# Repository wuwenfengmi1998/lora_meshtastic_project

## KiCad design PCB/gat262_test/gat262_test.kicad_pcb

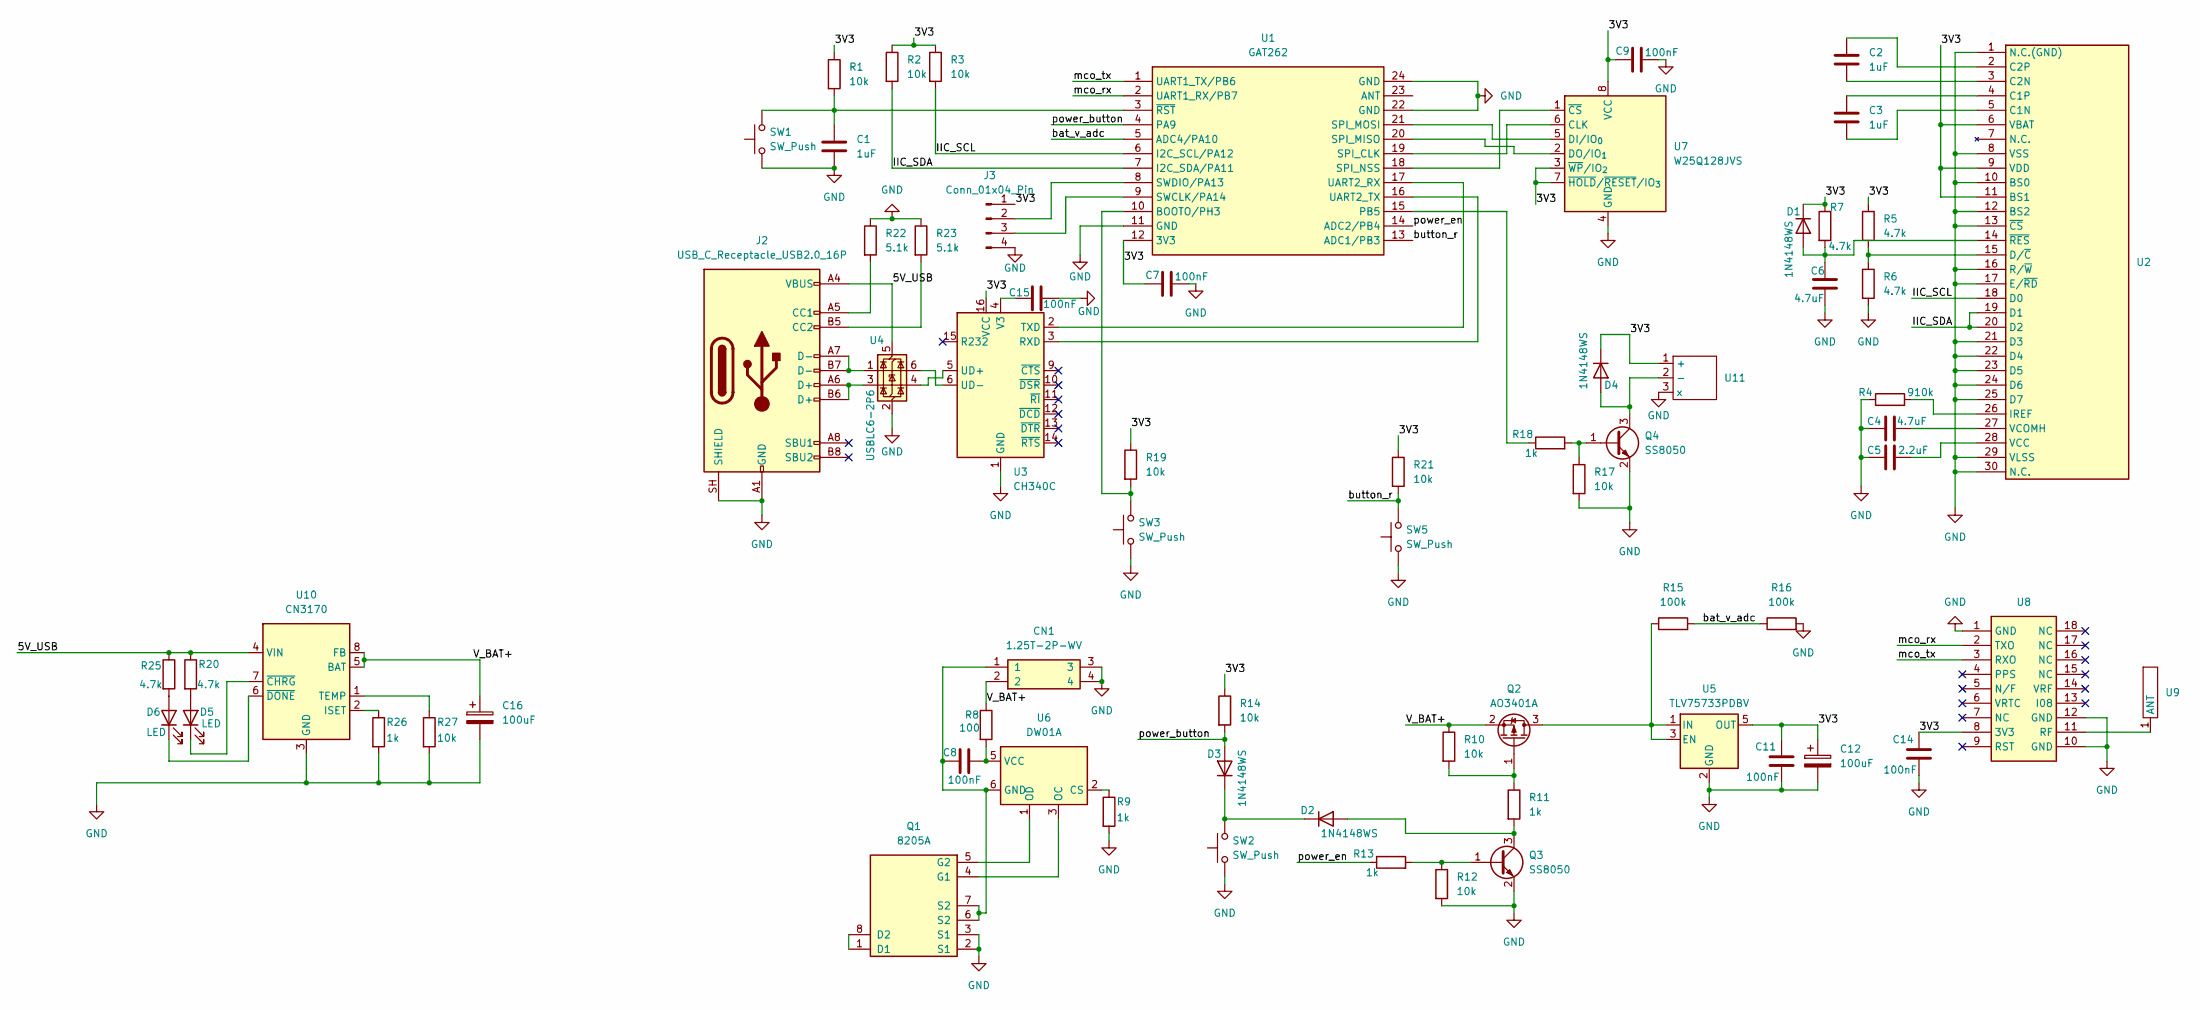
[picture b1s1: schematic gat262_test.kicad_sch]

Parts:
C1, C2, C3: 1uF; C_0805_2012Metric
C4, C6: 4.7uF; C_0805_2012Metric
C5: 2.2uF; C_0805_2012Metric
C7, C8, C9, C11, C14, C15: 100nF; C_0805_2012Metric
C12, C16: 100uF; CP_Elec_5x5.4
CN1: 1.25T-2P-WV; MPN 1.25T-2P-WV
D1, D2, D3, D4: 1N4148WS; D_SOD-323_HandSoldering
D5, D6: LED; LED_0603_1608Metric
J2: USB_C_Receptacle_USB2.0_16P; USB_C_Receptacle_G-Switch_GT-USB-7010ASV
J3: Conn_01x04_Pin; PinSocket_1x04_P2.54mm_Vertical
Q1: 8205A; MPN 8205A
Q2: AO3401A; SOT-23
Q3, Q4: SS8050; SOT-23-3
R1, R2, R3, R10, R12, R14, R17, R19, R21, R27: 10k; R_0603_1608Metric
R4: 910k; R_0603_1608Metric
R5, R6, R7, R20, R25: 4.7k; R_0603_1608Metric
R8: 100; R_0603_1608Metric
R9, R11, R13, R18, R26: 1k; R_0603_1608Metric
R15, R16: 100k; R_0603_1608Metric
R22, R23: 5.1k; R_0603_1608Metric
SW1, SW2, SW3, SW5: SW_Push; SW_SPST_B3U-1000P
U1: GAT262
U2: OLED_128_64
U3: CH340C; SOIC-16_3.9x9.9mm_P1.27mm
U4: USBLC6-2P6; SOT-23-6
U5: TLV75733PDBV; SOT-23-5
U6: DW01A; SOT-23-6
U7: W25Q128JVS; SOIC-8_5.3x5.3mm_P1.27mm
U8: gp02
U9: gps天线
U10: CN3170; SOIC-8-1EP_3.9x4.9mm_P1.27mm_EP2.41x3.3mm_ThermalVias
U11: 5050蜂鸣器

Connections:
/3V3: C7.1, C9.1, C11.2, C12.1, C14.2, D1.1 (K), D4.1 (K), J3.1, R1.1, R2.1, R3.1, R5.1, R7.1, R14.1, R19.1, R21.1, U1.12 (3V3), U2.6 (VBAT), U2.9 (VDD), U2.11 (BS1), U3.16 (VCC), U5.5 (OUT), U7.3 (~WP/IO_{2}), U7.7 (~HOLD/~RESET/IO_{3}), U7.8 (VCC), U8.8 (3V3), U11.1 (+)
/5V_USB: J2.A4 (VBUS), J2.A9 (VBUS), J2.B4 (VBUS), J2.B9 (VBUS), R20.1, R25.1, U4.5 (VBUS), U10.4 (VIN)
/IIC_SCL: R3.2, U1.6 (I2C_SCL/PA12), U2.18 (D0)
/IIC_SDA: R2.2, U1.7 (I2C_SDA/PA11), U2.19 (D1), U2.20 (D2)
/V_BAT+: C16.1, CN1.2, Q2.2 (S), R8.1, R10.1, U10.5 (BAT), U10.8 (FB)
/bat_v_adc: R15.2, R16.1, U1.5 (ADC4/PA10)
/button_r: R21.2, SW5.2, U1.13 (ADC1/PB3)
/mco_rx: U1.2 (UART1_RX/PB7), U8.2 (TXO)
/mco_tx: U1.1 (UART1_TX/PB6), U8.3 (RXO)
/power_button: D3.2 (A), R14.2, U1.4 (PA9)
/power_en: R13.1, U1.14 (ADC2/PB4)
GND: C1.2, C4.1, C5.1, C6.1, C7.2, C9.2, C11.1, C12.2, C14.1, C15.2, C16.2, CN1.3, CN1.4, J2.A1 (GND), J2.A12 (GND), J2.B1 (GND), J2.B12 (GND), J2.SH (SHIELD), J3.4, Q1.2 (S1), Q1.3 (S1), Q3.2 (E), Q4.2 (E), R4.1, R6.2, R9.2, R12.2, R16.2, R17.2, R22.1, R23.1, R26.2, R27.2, SW1.1, SW2.1, SW3.1, SW5.1, U1.11 (GND), U1.22 (GND), U1.24 (GND), U2.1 (N.C.(GND)), U2.8 (VSS), U2.10 (BS0), U2.12 (BS2), U2.13 (~CS), U2.16 (R/~W), U2.17 (E/~RD), U2.21 (D3), U2.22 (D4), U2.23 (D5), U2.24 (D6), U2.25 (D7), U2.29 (VLSS), U2.30 (N.C.), U3.1 (GND), U4.2 (GND), U5.2 (GND), U7.4 (GND), U8.1 (GND), U8.10 (GND), U8.12 (GND), U10.3 (GND), U10.9 (GND), U11.3 (x)
unnamed: C6.2, D1.2 (A), R7.2, U2.14 (~RES)
unnamed: D2.2 (A), Q3.3 (C), R11.2
unnamed: D2.1 (K), D3.1 (K), SW2.2
unnamed: D4.2 (A), Q4.3 (C), U11.2 (-)
unnamed: D5.2 (A), R20.2
unnamed: D5.1 (K), U10.7 (~CHRG)
unnamed: D6.2 (A), R25.2
unnamed: D6.1 (K), U10.6 (~DONE)
unnamed: J2.A5 (CC1), R22.2
unnamed: J2.B5 (CC2), R23.2
unnamed: J2.A6 (D+), J2.B6 (D+), U4.3 (I/O2)
unnamed: J2.A7 (D-), J2.B7 (D-), U4.1 (I/O1)
unnamed: J3.2, U1.8 (SWDIO/PA13)
unnamed: J3.3, U1.9 (SWCLK/PA14)
unnamed: Q1.1 (D1), Q1.8 (D2)
unnamed: Q1.4 (G1), U6.3 (OC)
unnamed: Q1.5 (G2), U6.1 (OD)
unnamed: Q2.3 (D), R15.1, U5.1 (IN), U5.3 (EN)
unnamed: Q2.1 (G), R10.2, R11.1
unnamed: Q3.1 (B), R12.1, R13.2
unnamed: Q4.1 (B), R17.1, R18.2
unnamed: R19.2, SW3.2, U1.10 (BOOTO/PH3)
unnamed: R18.1, U1.15 (PB5)
unnamed: U1.19 (SPI_CLK), U7.6 (CLK)
unnamed: U1.20 (SPI_MISO), U7.2 (DO/IO_{1})
unnamed: U1.21 (SPI_MOSI), U7.5 (DI/IO_{0})
unnamed: U1.18 (SPI_NSS), U7.1 (~CS)
unnamed: U1.17 (UART2_RX), U3.2 (TXD)
unnamed: U1.16 (UART2_TX), U3.3 (RXD)
unnamed: C1.1, R1.2, SW1.2, U1.3 (~RST)
unnamed: C3.2, U2.5 (C1N)
unnamed: C3.1, U2.4 (C1P)
unnamed: C2.2, U2.3 (C2N)
unnamed: C2.1, U2.2 (C2P)
unnamed: R5.2, R6.1, U2.15 (D/~C)
unnamed: R4.2, U2.26 (IREF)
unnamed: C5.2, U2.28 (VCC)
unnamed: C4.2, U2.27 (VCOMH)
unnamed: U3.5 (UD+), U4.4 (I/O2)
unnamed: U3.6 (UD-), U4.6 (I/O1)
unnamed: C15.1, U3.4 (V3)
unnamed: R9.1, U6.2 (CS)
unnamed: C8.1, CN1.1, Q1.6 (S2), Q1.7 (S2), U6.6 (GND)
unnamed: C8.2, R8.2, U6.5 (VCC)
unnamed: U8.11 (RF), U9.1 (ANT_1)
unnamed: R26.1, U10.2 (ISET)
unnamed: R27.1, U10.1 (TEMP)

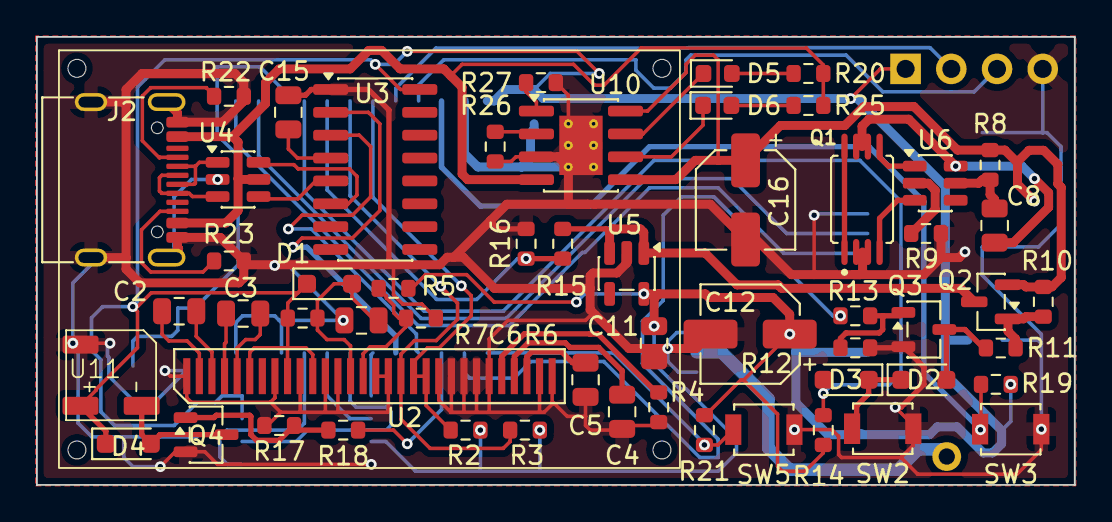
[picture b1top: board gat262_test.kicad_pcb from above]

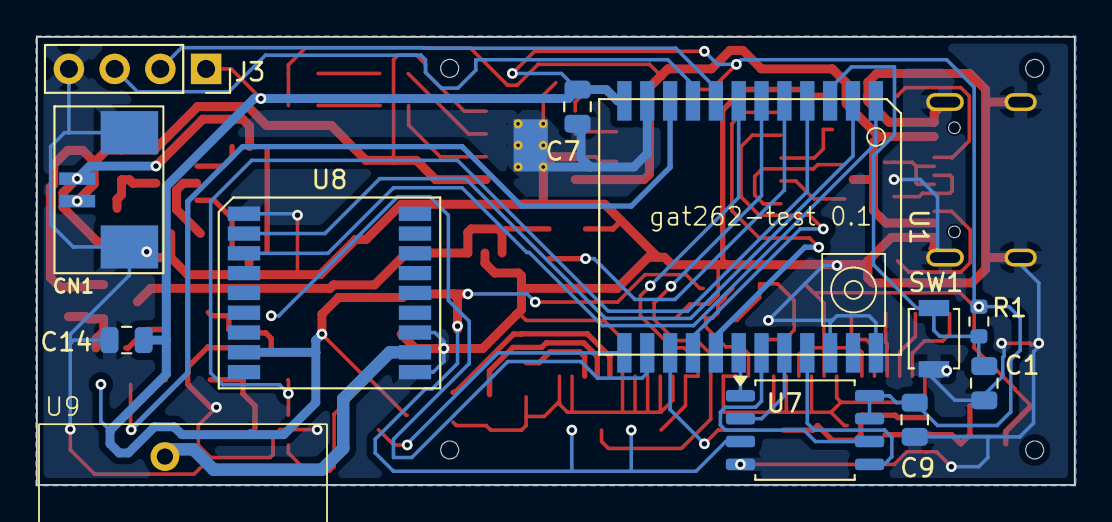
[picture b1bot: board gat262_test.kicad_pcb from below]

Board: 2 copper layers, 57.7 x 24.9 mm, 68 parts (12 on the bottom side), 59 nets.

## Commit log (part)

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2026-02-19 Add Demo Signed-off-by: kevin <kevin@lmve.net>
2026-02-20 已绘制原理图
2026-02-21 PCB 已完成 Signed-off-by: kevin <kevin@lmve.net>
2026-02-21 MV 版本原理图完成 Signed-off-by: kevin <kevin@lmve.net>
2026-02-22 MV版本PCBOK Signed-off-by: kevin <kevin@lmve.net>
2026-02-27 加入技术手册 Signed-off-by: 吴文峰 <kevin@lmve.net>
2026-03-02 PCB 更新到版本2 Signed-off-by: 吴文峰 <kevin@lmve.net>
2026-03-04 增加mv版本
2026-03-04 增加SETTING_MAX_POWER参数，
2026-03-04 增加屏幕支持
2026-03-04 加入GPS
2026-03-04 加入adc 加入led
2026-03-06 up Signed-off-by: 吴文峰 <kevin@lmve.net>
2026-03-06 稳定版代码 Signed-off-by: 吴文峰 <kevin@lmve.net>
2026-03-06 加密似乎ok了
2026-03-09 增加e22-400M33S Signed-off-by: kevin <kevin@lmve.net>
2026-03-09 3D Signed-off-by: kevin <kevin@lmve.net>
2026-03-19 新版本原理图 Signed-off-by: 吴文峰 <kevin@lmve.net>
2026-03-19 旅行版PCB画完 Signed-off-by: 吴文峰 <kevin@lmve.net>
2026-03-21 SETTING_MAX_POWER
2026-03-22 修复固件功率bug 实际功率需要用户自行计算 Signed-off-by: kevin <kevin@lmve.net>
2026-03-28 feat(travelers): TCA9535 矩阵键盘驱动 + 电源管理 + LoRa RST 虚拟引脚
    - 新增 TCA9535ButtonThread 驱动 (4x4 矩阵键盘, 中断/轮询模式)
    - 电源管理: P1.2 POWER_EN (MOS 供电) + P1.3 POWER_BOOT (2s 开/关机)
    - LoRa RST 通过 TCA9535 P1.4 + TCA9535GpioHal 虚拟引脚 200 控制
    - 修复 LTO 链接错误 (去掉 .h/.cpp 中的 HAS_TCA9535_BUTTON 守卫)
    - 新增 CHANGELOG.md, 更新 readme.md (PCAL9535 升级计划)
2026-03-28 feat(travelers): 矩阵按键映射改为 key3/7/11/15 方向键, P1.5 独立闪烁, 修复 cols 整数提升 bug
2026-03-28 feat(travelers): enable GPS with GP-02 module support
    - Add HAS_GPS=1, GPS_RX_PIN=20, GPS_TX_PIN=21
    - Add TCA9535 P1.6 (GPS RST) and P1.7 (GPS EN) control via I2C
    - GPS power on at boot: P1.6 and P1.7 default HIGH in init
    - Bridge gps->enablePin to TCA9535 via GpioUnaryTransformer
    - Add tca9535GpsReset() and tca9535GpsEn() static functions
    - Update CHANGELOG with GPS support details
2026-03-29 feat(travelers): TCA9535 充电检测 + 键盘背光 + isVbusIn 修复
    - 新增 P1.1 CHARGE_DET 充电检测（高电平=充电中），轮询间隔 2s
    - Power.cpp isCharging()/isVbusIn() 均使用 TCA9535_CHARGE_DET_PIN 分支
    - 新增 P1.0 键盘背光（高电平点亮），按键时亮，5s 无操作自动熄灭
    - 修复开机供电维持：POWER_EN 在 Wire.begin() 后立即锁定
    - 修复 P1 config 寄存器值 0x0A（之前 0x8D 导致 P1.2 高阻断电）
    - ⚠️ 已知问题：TP4057 电压反串导致未充电时 P1.1 仍读高，需硬件修改
2026-03-29 feat: 开机确认窗口 + 快捷回复/九宫格导航 + 充电检测加速
2026-03-29 feat(T9): 九宫格输入法 + 多项 bug 修复
    - T9 multi-tap 输入法：abc/ABC/123 三模式切换
    - 修复 commitMultiTap 无限递归崩溃（重入保护）
    - 修复 payload 残留导致非预期行为
    - 修复 REGENERATE_FRAMESET 重复触发导致跳回主页面
    - 修复大小写模式下出现数字（t9LetterMap 重做）
    - 修复光标不跟随预览字符跳转（displayCursor +1）
2026-03-29 feat: add Chinese 12x12 bitmap font (21075 glyphs) and fix boot gate
    - Add ChineseFont12x12.h: U+4E00-U+9FFF CJK coverage, 535KB flash
    - Add gen_chinese_font.mjs: @napi-rs/canvas based font generator tool
    - Enable CJK rendering in MessageRenderer and CannedMessageModule
    - Remove boot confirmation gate (required 2s button hold, caused shutdown loop)
    - Update partition table: app 2.75MB, OTA 192KB, spiffs 1MB
    - Update CHANGELOG
2026-03-29 up，中文字符显示向下挪动两个像素
2026-03-30 fix: 修复 NodeInfo 不广播节点名字和公钥问题
    - AdminModule: 显式同步 owner.role = config.device.role
    - NodeDB: CLIENT/CLIENT_MUTE 切回后恢复广播间隔
    修复从 CLIENT_HIDDEN 切换回 CLIENT 后 NodeInfo 永不广播的问题
2026-03-30 feat: 主页按*进入自由文本输入模式
    - 移除 INACTIVE 状态下 UP/DOWN 按键触发快捷回复列表的逻辑
    - 按 * 键直接进入 FREETEXT 模式
2026-03-30 fix: 修复 INACTIVE 状态下 UP/DOWN 仍能进入快捷回复的问题
    - handleMessageSelectorInput() 在 INACTIVE 状态时直接返回 false
    - 按 * 键进入 FREETEXT 模式
2026-03-30 fix: 启用 CANNED_MESSAGE_MODULE_ENABLE
    - 在 variant.h 中添加 CANNED_MESSAGE_MODULE_ENABLE=1
    - 确保 CannedMessageModule 正确注册到 inputBroker
2026-03-30 debug: 添加 INACTIVE 状态输入事件日志
2026-03-30 debug: 添加 handleInputEvent 调用日志
2026-03-30 fix: * 键在空文本时作为普通字符而非退格键处理
    - 当 freetext 为空时，* 应该添加到文本中
    - 只有 freetext 有内容时，* 才作为退格键
2026-03-30 fix: 进入 FREETEXT 后不立即处理当前按键，避免多一个字符
    - 进入 FREETEXT 状态后返回 1 表示已处理，不调用 handleFreeTextInput
    - 用户下次按键时才会添加字符
2026-03-30 fix: 输入状态下 * 仅作为退格键，不输入字符
    - 移除 freetext.length() > 0 的条件判断
    - * 始终作为退格键处理
2026-03-30 up,需要画新PCB
2026-03-30 fix: 节点列表禁用自动切换，改为上下键控制
    - 禁用 autoCycleEnabled，停止自动切换模式
    - 添加 switchToNextMode/switchToPrevMode/getCurrentMode 函数
    - 在 Screen.cpp 中添加 UP/DOWN 按键处理来切换模式
2026-03-30 fix: 节点列表长按切换模式，短按不处理
    - 添加 onUpPressed/onDownPressed 记录按键时间
    - 在 drawDynamicNodeListScreen 中调用 checkLongPress() 检测长按
    - 长按(>500ms)切换模式，短按不处理
2026-03-30 fix: 节点列表改用双击切换模式\n\n- TCA9535 不支持长按事件，改用双击检测（400ms内连续两次按键）\n- 双击 UP：切换到上一个模式\n- 双击 DOWN：切换到下一个模式\n- 单击：保持原有行为（滚动界面）"
2026-03-30 fix: 节点列表单击滚动，双击切换模式\n\n- 单击 UP/DOWN：滚动界面\n- 双击（400ms内）：切换模式"
2026-03-30 fix: 修复节点列表滚动数组越界崩溃\n\n- scrollDown() 添加最大边界检查\n- 渲染函数中添加 startIndex 边界检查\n- 切换模式时重置滚动位置"
2026-03-30 fix: 添加 calculateMaxScroll 前向声明解决编译错误"
2026-03-30 feat: FREETEXT 模式添加滚动条和光标移动\n\n- 添加 textScrollOffset 变量跟踪滚动位置\n- UP/DOWN 按钮移动光标\n- 文本输入时自动滚动保持光标可见\n- 绘制滚动条显示当前位置\n- 进入 FREETEXT 时重置滚动偏移"
2026-04-06 二代mt画完 Signed-off-by: kevin <kevin@lmve.net>
2026-04-07 up Signed-off-by: kevin <kevin@lmve.net>
